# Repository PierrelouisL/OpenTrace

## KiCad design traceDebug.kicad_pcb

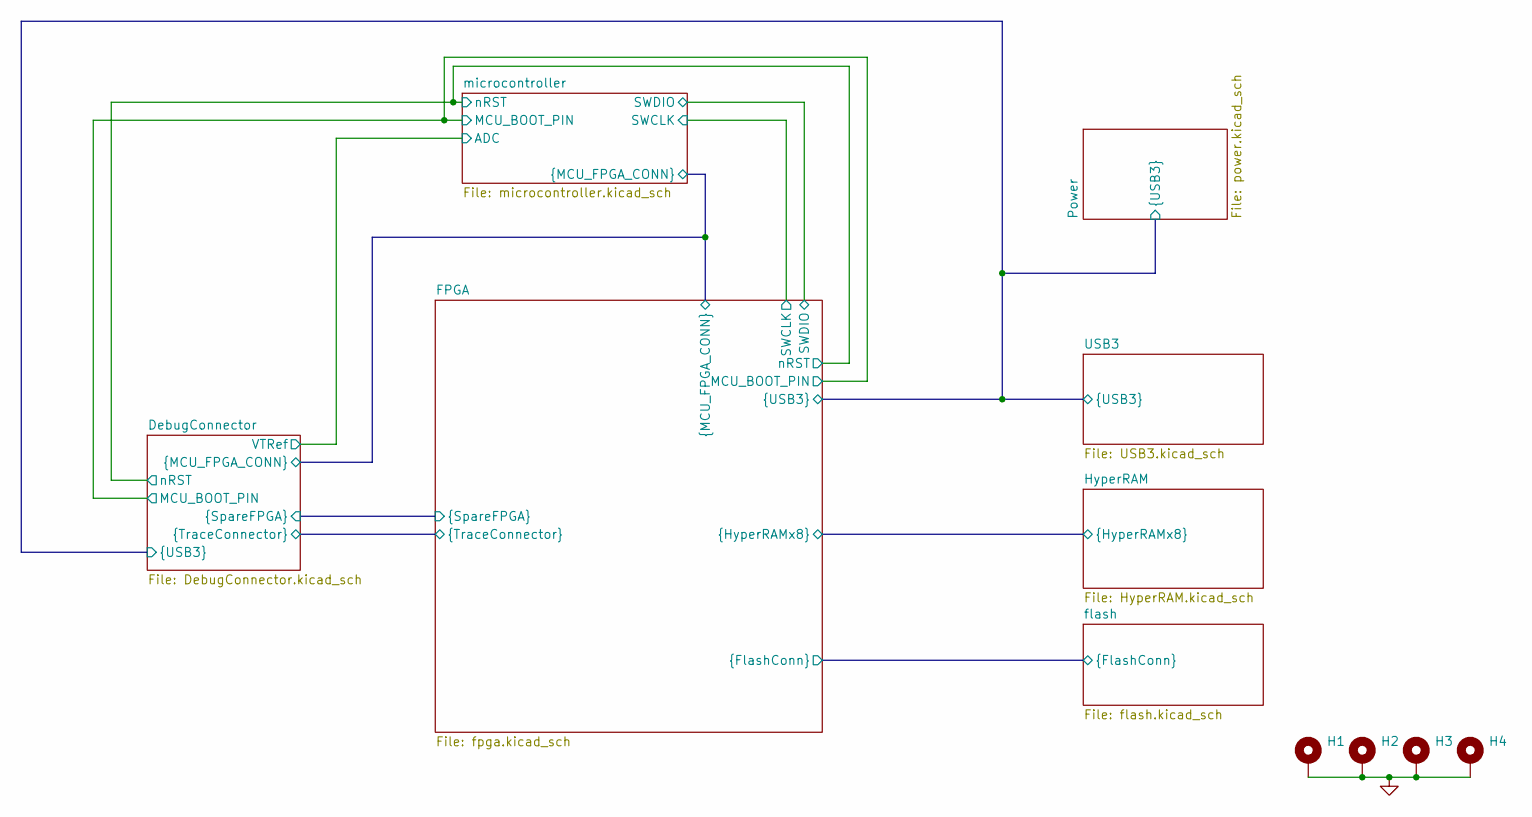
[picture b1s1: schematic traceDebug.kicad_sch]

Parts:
H1, H2, H3, H4: MountingHole_Pad; MountingHole_3.2mm_M3_Pad_Via

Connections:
GND: H1.1 (1_1), H2.1 (1_1), H3.1 (1_1), H4.1 (1_1); also elsewhere on the board

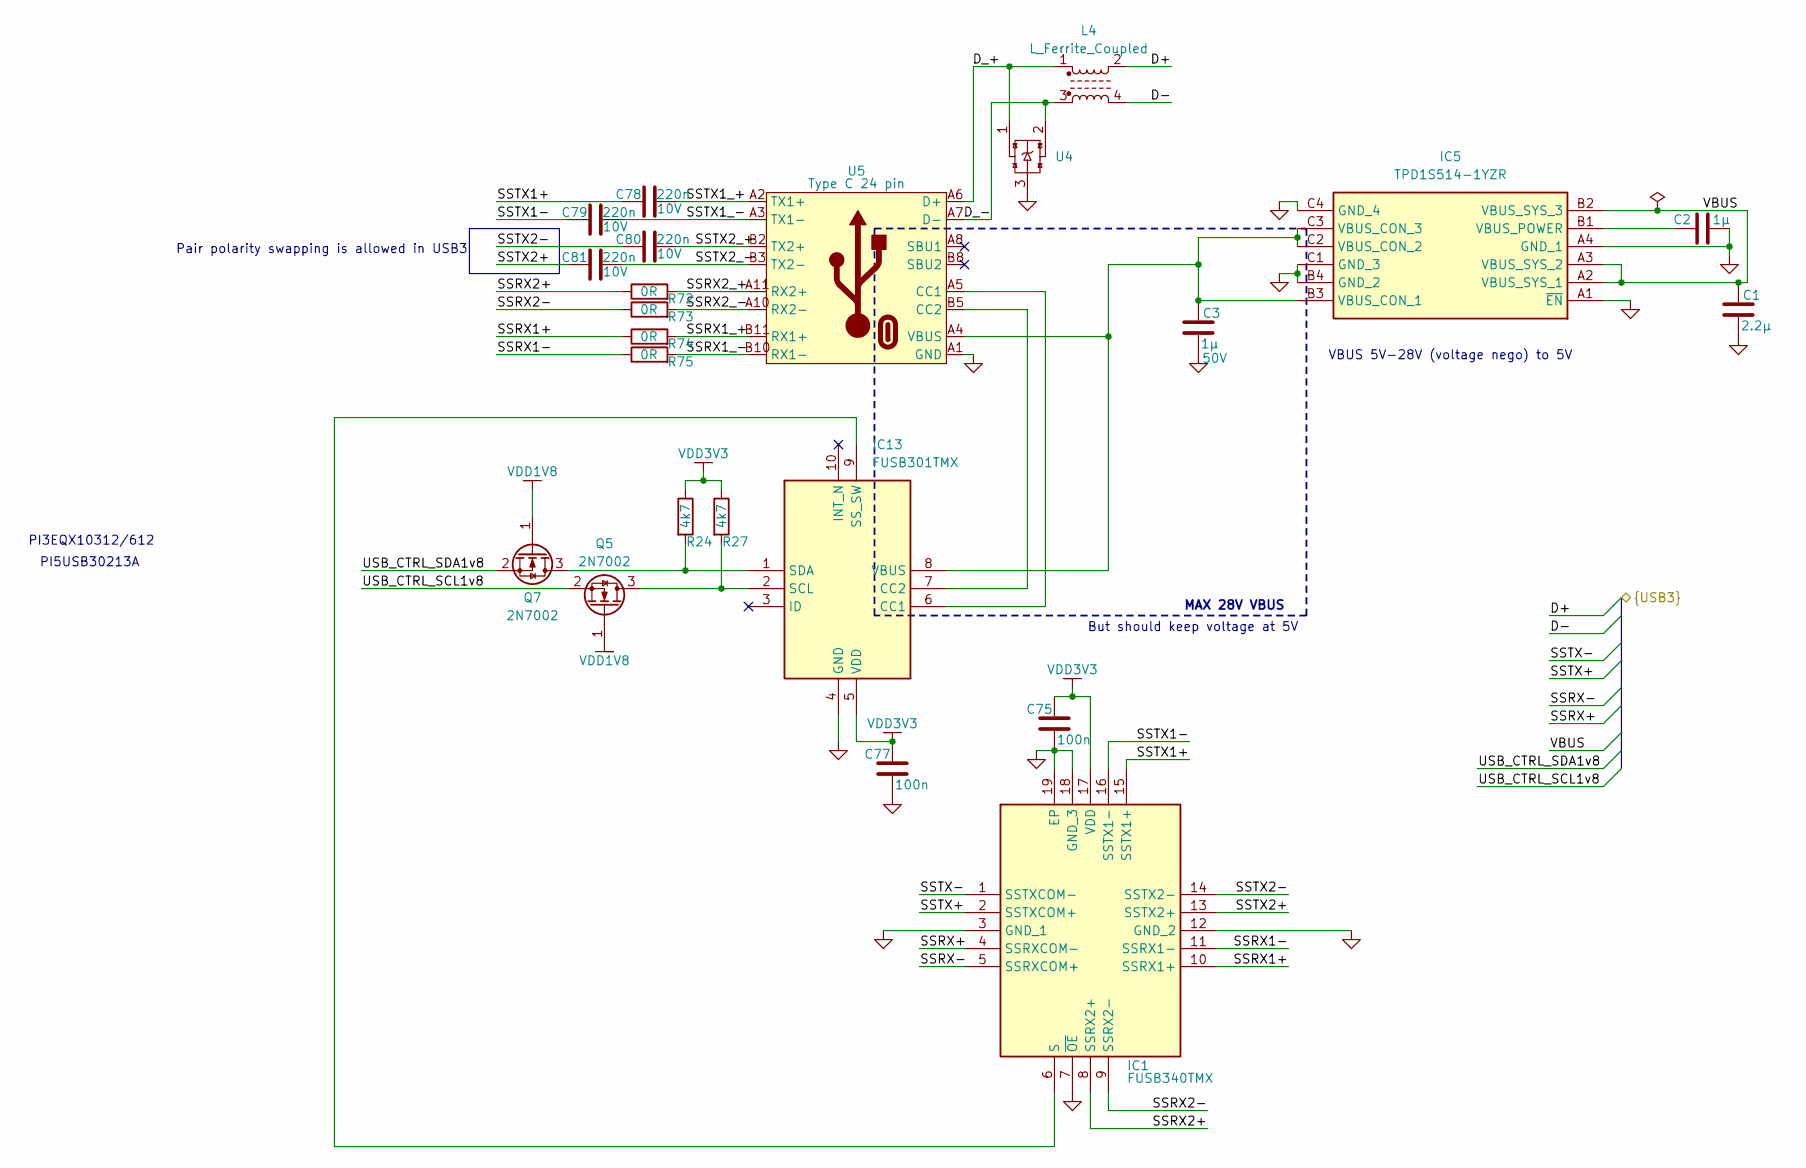
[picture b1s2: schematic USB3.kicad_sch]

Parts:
C1: 2.2µ; C_0402_1005Metric
C2: 1µ; C_0402_1005Metric
C3: 1µ; C_0402_1005Metric; Max voltage 50V
C75, C77: 100n; C_0402_1005Metric
C78, C79, C80, C81: 220n; C_0201_0603Metric; voltage 10V
IC1: FUSB340TMX; Manufacturer_Part_Number FUSB340TMX; Mouser Part Number 512-FUSB340TMX
IC5: TPD1S514-1YZR; BGA12C40P4X3_199X129X62; Manufacturer_Part_Number TPD1S514-1YZR; Mouser Part Number 595-TPD1S514-1YZR
IC13: FUSB301TMX; Manufacturer_Part_Number FUSB301TMX; Mouser Part Number 512-FUSB301TMX
L4: L_Ferrite_Coupled; C908339
Q5, Q7: 2N7002; SOT-23
R24, R27: 4k7; R_0402_1005Metric
R72, R73, R74, R75: 0R; R_0201_0603Metric
U4: C502577
U5: Type C 24 pin; USB3-2_C2762992; LCSC C2762992

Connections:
/DebugConnector/D+: L4.2; also elsewhere on the board
/DebugConnector/D-: L4.4; also elsewhere on the board
/DebugConnector/SSRX+: IC1.4 (SSRXCOM-); also elsewhere on the board
/DebugConnector/SSRX-: IC1.5 (SSRXCOM+); also elsewhere on the board
/DebugConnector/SSTX+: IC1.2 (SSTXCOM+); also elsewhere on the board
/DebugConnector/SSTX-: IC1.1 (SSTXCOM-); also elsewhere on the board
/DebugConnector/USB_CTRL_SCL1v8: Q5.2 (S); also elsewhere on the board
/DebugConnector/USB_CTRL_SDA1v8: Q7.2 (S); also elsewhere on the board
/DebugConnector/VBUS: C1.2, IC5.A2 (VBUS_SYS_1), IC5.A3 (VBUS_SYS_2), IC5.B2 (VBUS_SYS_3); also elsewhere on the board
/USB3/D_+: L4.1, U4.1, U5.A6 (D+), U5.B6 (D+)
/USB3/D_-: L4.3, U4.2, U5.A7 (D-), U5.B7 (D-)
/USB3/SSRX1+: IC1.10 (SSRX1+), R74.1
/USB3/SSRX1-: IC1.11 (SSRX1-), R75.1
/USB3/SSRX1_+: R74.2, U5.B11 (RX1+)
/USB3/SSRX1_-: R75.2, U5.B10 (RX1-)
/USB3/SSRX2+: IC1.8 (SSRX2+), R72.1
/USB3/SSRX2-: IC1.9 (SSRX2-), R73.1
/USB3/SSRX2_+: R72.2, U5.A11 (RX2+)
/USB3/SSRX2_-: R73.2, U5.A10 (RX2-)
/USB3/SSTX1+: C78.1, IC1.15 (SSTX1+)
/USB3/SSTX1-: C79.1, IC1.16 (SSTX1-)
/USB3/SSTX1_+: C78.2, U5.A2 (TX1+)
/USB3/SSTX1_-: C79.2, U5.A3 (TX1-)
/USB3/SSTX2+: C81.1, IC1.13 (SSTX2+)
/USB3/SSTX2-: C80.1, IC1.14 (SSTX2-)
/USB3/SSTX2_+: C80.2, U5.B2 (TX2+)
/USB3/SSTX2_-: C81.2, U5.B3 (TX2-)
GND: C1.1, C2.1, C3.1, C75.2, C77.2, IC1.3 (GND_1), IC1.7 (~OE), IC1.12 (GND_2), IC1.18 (GND_3), IC1.19 (EP), IC5.A1 (~EN), IC5.A4 (GND_1), IC5.B4 (GND_2), IC5.C1 (GND_3), IC5.C4 (GND_4), IC13.4 (GND), U4.3, U5.25 (GND), U5.26 (GND), U5.27 (GND), U5.28 (GND), U5.A1 (GND), U5.A12 (GND), U5.B1 (GND), U5.B12 (GND); also elsewhere on the board
unnamed: IC1.6 (S), IC13.9 (SS_SW)
unnamed: C2.2, IC5.B1 (VBUS_POWER)
unnamed: IC13.6 (CC1), U5.A5 (CC1)
unnamed: IC13.7 (CC2), U5.B5 (CC2)
unnamed: IC13.2 (SCL), Q5.3 (D), R27.2
unnamed: IC13.1 (SDA), Q7.3 (D), R24.2
unnamed: C3.2, IC5.B3 (VBUS_CON_1), IC5.C2 (VBUS_CON_2), IC5.C3 (VBUS_CON_3), IC13.8 (VBUS), U5.A4 (VBUS), U5.A9 (VBUS), U5.B4 (VBUS), U5.B9 (VBUS)
VDD1V8: Q5.1 (G), Q7.1 (G); also elsewhere on the board
VDD3V3: C75.1, C77.1, IC1.17 (VDD), IC13.5 (VDD), R24.1, R27.1; also elsewhere on the board

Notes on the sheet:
PI5USB30213A
MAX 28V VBUS
But should keep voltage at 5V
VBUS 5V-28V (voltage nego) to 5V
Pair polarity swapping is allowed in USB3
PI3EQX10312/612

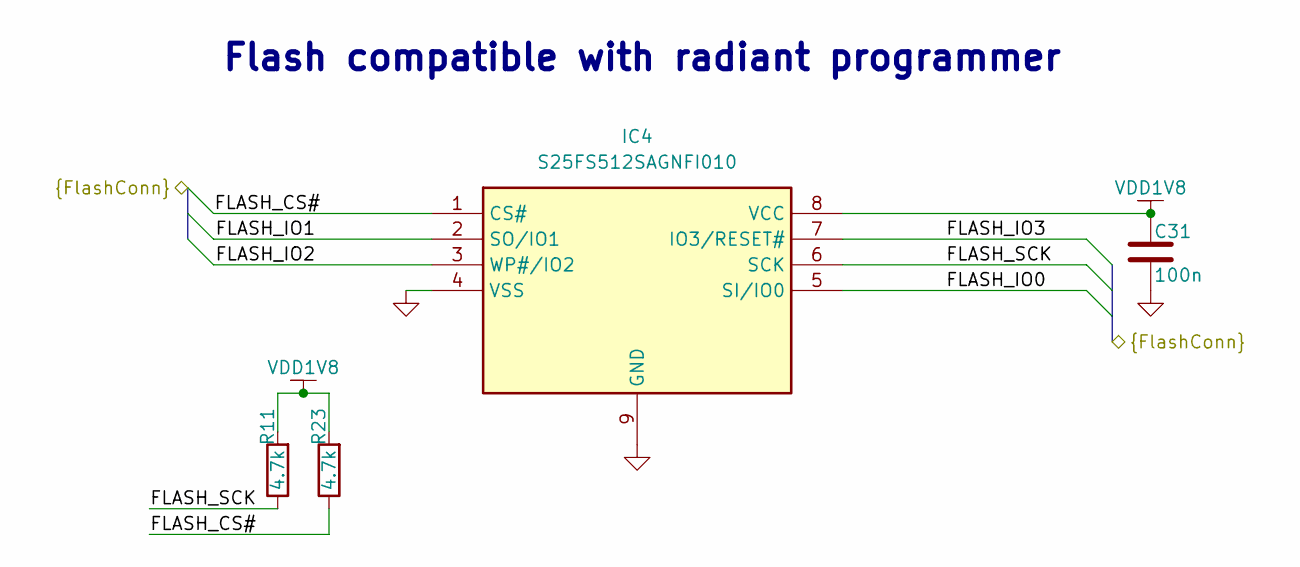
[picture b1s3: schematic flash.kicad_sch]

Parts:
C31: 100n; C_0402_1005Metric
IC4: S25FS512SAGNFI010; SON127P800X600X80-9N-D; Manufacturer_Part_Number S25FS512SAGNFI010; Mouser Part Number 727-25FS512SAGNFI010
R11, R23: 4.7k; R_0402_1005Metric

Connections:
/FPGA/FLASH_CS#: IC4.1 (CS#), R23.1; also elsewhere on the board
/FPGA/FLASH_IO0: IC4.5 (SI/IO0); also elsewhere on the board
/FPGA/FLASH_IO1: IC4.2 (SO/IO1); also elsewhere on the board
/FPGA/FLASH_IO2: IC4.3 (WP#/IO2); also elsewhere on the board
/FPGA/FLASH_IO3: IC4.7 (IO3/RESET#); also elsewhere on the board
/FPGA/FLASH_SCK: IC4.6 (SCK), R11.1; also elsewhere on the board
GND: C31.2, IC4.4 (VSS), IC4.9 (GND); also elsewhere on the board
VDD1V8: C31.1, IC4.8 (VCC), R11.2, R23.2; also elsewhere on the board

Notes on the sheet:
Flash compatible with radiant programmer

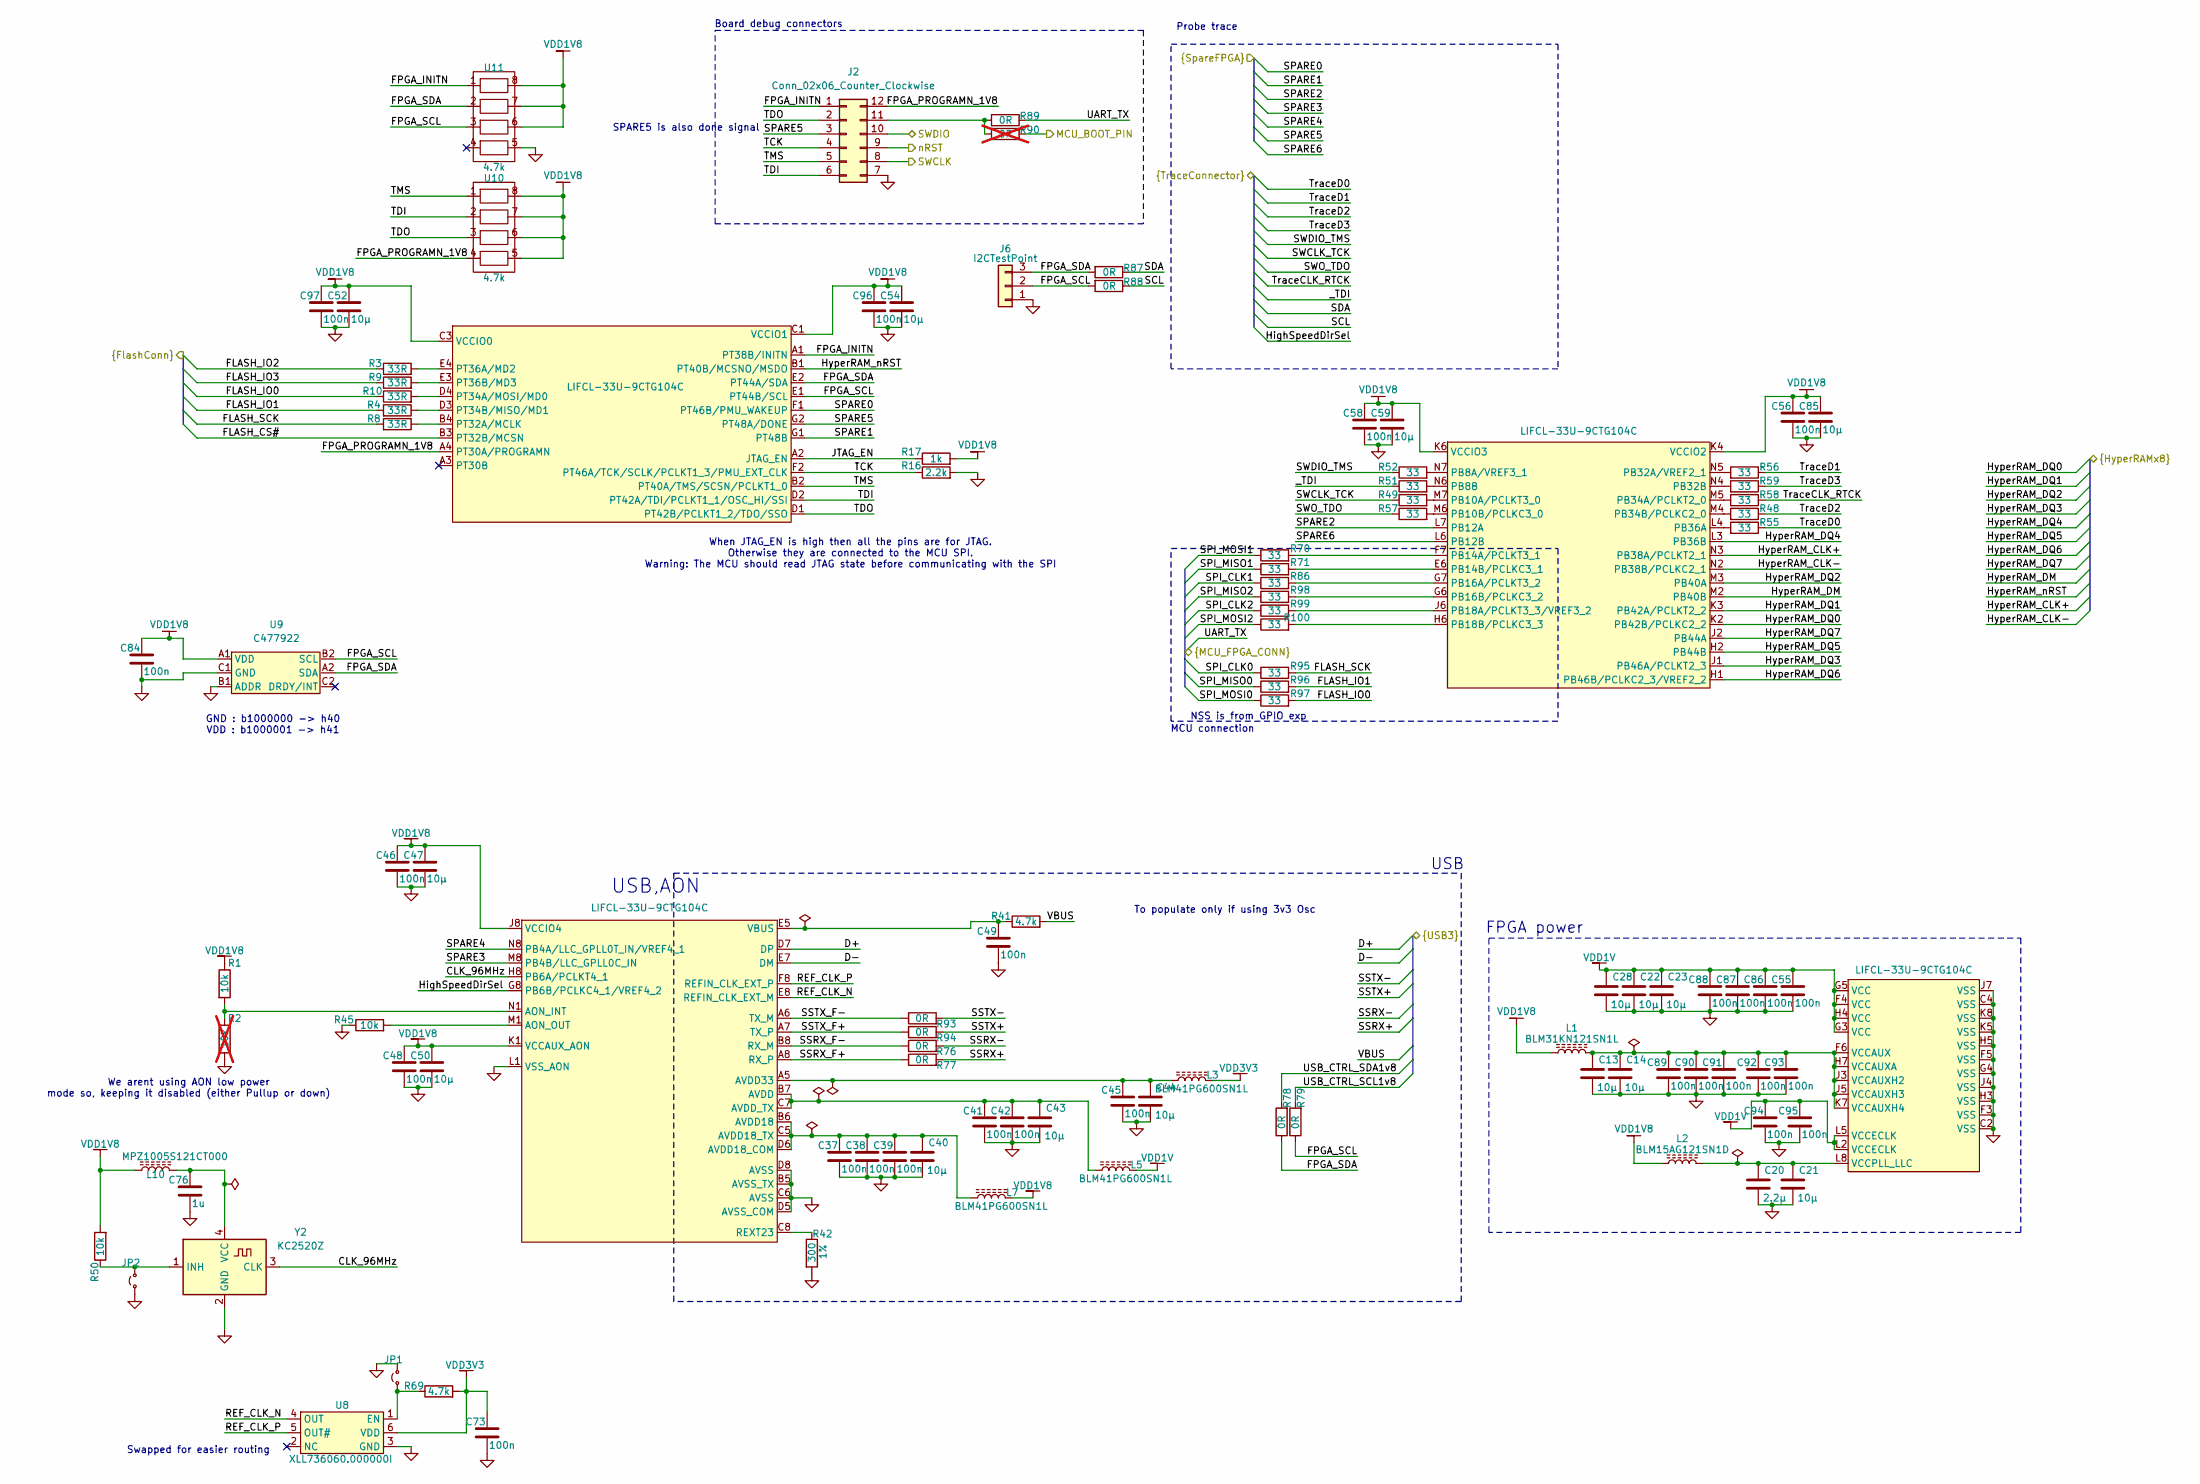
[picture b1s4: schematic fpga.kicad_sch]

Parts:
C13, C14, C21, C22, C23, C28, C40, C43, C44, C47, C50, C52, C54, C59, C85: 10µ; C_0402_1005Metric
C20: 2.2µ; C_0402_1005Metric
C37, C38, C39, C41, C42, C45, C46, C48, C49, C55, C56, C58, C86, C87, C88, C89, C90, C91, C92, C93, C94, C95, C96, C97: 100n; C_0201_0603Metric
C73, C84: 100n; C_0402_1005Metric
C76: 1u; C_0402_1005Metric
J2: Conn_02x06_Counter_Clockwise; PinHeader_2x06_P2.54mm_Vertical
J6: I2CTestPoint; PinHeader_1x03_P2.54mm_Vertical
JP1, JP2: Jumper_2_Small_Open; PinHeader_1x02_P2.54mm_Vertical
L1: BLM31KN121SN1L; L_1206_3216Metric
L2: BLM15AG121SN1D; L_0402_1005Metric
L3, L5, L7: BLM41PG600SN1L; L_1806_4516Metric
L10: MPZ1005S121CT000; L_0402_1005Metric
R1, R45, R50: 10k; R_0402_1005Metric
R2: 10k; R_0402_1005Metric; not fitted
R3, R4, R8, R9, R10: 33R; R_0402_1005Metric
R16: 2.2k; R_0402_1005Metric
R17: 1k; R_0402_1005Metric
R41, R69: 4.7k; R_0402_1005Metric
R42: 300; R_0402_1005Metric
R48, R49, R51, R52, R55, R56, R57, R58, R59, R70, R71, R86, R95, R96, R97, R98, R99, R100: 33; R_0402_1005Metric
R76, R77, R93, R94: 0R; R_0201_0603Metric
R78, R79, R87, R88, R89: 0R; R_0402_1005Metric
R90: 0R; R_0402_1005Metric; not fitted
U1: LIFCL-33U-9CTG104C; BGA104C65P8X13_550X850X97
U8: XLL736060.000000I; Renesas_XLL
U9: C477922; DSBGA-6; LCSC C477922
U10, U11: 4.7k; C876943; LCSC C876943
Y2: KC2520Z; Oscillator_SMD_Kyocera_KC2520Z-4Pin_2.5x2.0mm; mouser ref KC2520Z96.0000C1KX00

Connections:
/DebugConnector/D+: U1.D7 (DP); also elsewhere on the board
/DebugConnector/D-: U1.E7 (DM); also elsewhere on the board
/DebugConnector/HighSpeedDirSel: U1.G8 (PB6B/PCLKC4_1/VREF4_2); also elsewhere on the board
/DebugConnector/MCU_BOOT_PIN: R90.1; also elsewhere on the board
/DebugConnector/SCL: R88.1; also elsewhere on the board
/DebugConnector/SDA: R87.1; also elsewhere on the board
/DebugConnector/SPARE0: U1.F1 (PT46B/PMU_WAKEUP); also elsewhere on the board
/DebugConnector/SPARE1: U1.G1 (PT48B); also elsewhere on the board
/DebugConnector/SPARE2: U1.L7 (PB12A); also elsewhere on the board
/DebugConnector/SPARE3: U1.M8 (PB4B/LLC_GPLL0C_IN); also elsewhere on the board
/DebugConnector/SPARE4: U1.N8 (PB4A/LLC_GPLL0T_IN/VREF4_1); also elsewhere on the board
/DebugConnector/SPARE5: J2.3, U1.G2 (PT48A/DONE); also elsewhere on the board
/DebugConnector/SPARE6: U1.L6 (PB12B); also elsewhere on the board
/DebugConnector/SPI_CLK0: R95.1; also elsewhere on the board
/DebugConnector/SPI_CLK1: R86.1; also elsewhere on the board
/DebugConnector/SPI_CLK2: R99.1; also elsewhere on the board
/DebugConnector/SPI_MISO0: R96.1; also elsewhere on the board
/DebugConnector/SPI_MISO1: R71.1; also elsewhere on the board
/DebugConnector/SPI_MISO2: R98.1; also elsewhere on the board
/DebugConnector/SPI_MOSI0: R97.1; also elsewhere on the board
/DebugConnector/SPI_MOSI1: R70.1; also elsewhere on the board
/DebugConnector/SPI_MOSI2: R100.1; also elsewhere on the board
/DebugConnector/SSRX+: R77.2; also elsewhere on the board
/DebugConnector/SSRX-: R76.2; also elsewhere on the board
/DebugConnector/SSTX+: R94.2; also elsewhere on the board
/DebugConnector/SSTX-: R93.2; also elsewhere on the board
/DebugConnector/SWCLK_TCK: R49.1; also elsewhere on the board
/DebugConnector/SWDIO_TMS: R52.1; also elsewhere on the board
/DebugConnector/SWO_TDO: R57.1; also elsewhere on the board
/DebugConnector/TraceCLK_RTCK: R58.1; also elsewhere on the board
/DebugConnector/TraceD0: R55.1; also elsewhere on the board
/DebugConnector/TraceD1: R56.1; also elsewhere on the board
/DebugConnector/TraceD2: R48.1; also elsewhere on the board
/DebugConnector/TraceD3: R59.1; also elsewhere on the board
/DebugConnector/UART_TX: R89.1; also elsewhere on the board
/DebugConnector/USB_CTRL_SCL1v8: R79.2; also elsewhere on the board
/DebugConnector/USB_CTRL_SDA1v8: R78.2; also elsewhere on the board
/DebugConnector/VBUS: R41.2; also elsewhere on the board
/DebugConnector/_TDI: R51.1; also elsewhere on the board
/DebugConnector/nRST: J2.9; also elsewhere on the board
/FPGA/CLK_96MHz: U1.H8 (PB6A/PCLKT4_1), Y2.3 (CLK)
/FPGA/FLASH_CS#: U1.B3 (PT32B/MCSN); also elsewhere on the board
/FPGA/FLASH_IO0: R10.1, R97.2; also elsewhere on the board
/FPGA/FLASH_IO1: R4.2, R96.2; also elsewhere on the board
/FPGA/FLASH_IO2: R3.1; also elsewhere on the board
/FPGA/FLASH_IO3: R9.1; also elsewhere on the board
/FPGA/FLASH_SCK: R8.2, R95.2; also elsewhere on the board
/FPGA/FPGA_INITN: J2.1, U1.A1 (PT38B/INITN), U11.1
/FPGA/FPGA_PROGRAMN_1V8: J2.12, U1.A4 (PT30A/PROGRAMN), U10.4
/FPGA/FPGA_SCL: J6.2, R79.1, R88.2, U1.E1 (PT44B/SCL), U9.B2 (SCL), U11.3
/FPGA/FPGA_SDA: J6.3, R78.1, R87.2, U1.E2 (PT44A/SDA), U9.A2 (SDA), U11.2
/FPGA/HyperRAM_CLK+: U1.N3 (PB38A/PCLKT2_1); also elsewhere on the board
/FPGA/HyperRAM_CLK-: U1.N2 (PB38B/PCLKC2_1); also elsewhere on the board
/FPGA/HyperRAM_DM: U1.M2 (PB40B); also elsewhere on the board
/FPGA/HyperRAM_DQ0: U1.K2 (PB42B/PCLKC2_2); also elsewhere on the board
/FPGA/HyperRAM_DQ1: U1.K3 (PB42A/PCLKT2_2); also elsewhere on the board
/FPGA/HyperRAM_DQ2: U1.M3 (PB40A); also elsewhere on the board
/FPGA/HyperRAM_DQ3: U1.J1 (PB46A/PCLKT2_3); also elsewhere on the board
/FPGA/HyperRAM_DQ4: U1.L3 (PB36B); also elsewhere on the board
/FPGA/HyperRAM_DQ5: U1.H2 (PB44B); also elsewhere on the board
/FPGA/HyperRAM_DQ6: U1.H1 (PB46B/PCLKC2_3/VREF2_2); also elsewhere on the board
/FPGA/HyperRAM_DQ7: U1.J2 (PB44A); also elsewhere on the board
/FPGA/HyperRAM_nRST: U1.B1 (PT40B/MCSNO/MSDO); also elsewhere on the board
/FPGA/JTAG_EN: R17.1, U1.A2 (JTAG_EN)
/FPGA/REF_CLK_N: U1.E8 (REFIN_CLK_EXT_M), U8.4 (OUT)
/FPGA/REF_CLK_P: U1.F8 (REFIN_CLK_EXT_P), U8.5 (OUT#)
/FPGA/SSRX_F+: R77.1, U1.A8 (RX_P)
/FPGA/SSRX_F-: R76.1, U1.B8 (RX_M)
/FPGA/SSTX_F+: R94.1, U1.A7 (TX_P)
/FPGA/SSTX_F-: R93.1, U1.A6 (TX_M)
/FPGA/TCK: J2.4, R16.1, U1.F2 (PT46A/TCK/SCLK/PCLKT1_3/PMU_EXT_CLK)
/FPGA/TDI: J2.6, U1.D2 (PT42A/TDI/PCLKT1_1/OSC_HI/SSI), U10.2
/FPGA/TDO: J2.2, U1.D1 (PT42B/PCLKT1_2/TDO/SSO), U10.3
/FPGA/TMS: J2.5, U1.B2 (PT40A/TMS/SCSN/PCLKT1_0), U10.1
/microcontroller/SWCLK: J2.8; also elsewhere on the board
/microcontroller/SWDIO: J2.10; also elsewhere on the board
GND: C13.2, C14.2, C20.2, C21.2, C22.2, C23.2, C28.2, C37.2, C38.2, C39.2, C40.2, C41.2, C42.2, C43.2, C44.2, C45.2, C46.2, C47.2, C48.2, C49.2, C50.2, C52.2, C54.2, C55.2, C56.2, C58.2, C59.2, C73.2, C76.2, C84.2, C85.2, C86.2, C87.2, C88.2, C89.2, C90.2, C91.2, C92.2, C93.2, C94.2, C95.2, C96.2, C97.2, J2.7, J6.1, JP1.2 (B), JP2.1 (A), R2.2, R16.2, R42.2, R45.1, U1.B5 (AVSS_TX), U1.C2 (VSS), U1.C4 (VSS), U1.C6 (AVSS), U1.D5 (AVSS_COM), U1.D8 (AVSS), U1.F3 (VSS), U1.F5 (VSS), U1.G4 (VSS), U1.H3 (VSS), U1.H5 (VSS), U1.J4 (VSS), U1.J7 (VSS), U1.K5 (VSS), U1.K8 (VSS), U1.L1 (VSS_AON), U8.3 (GND), U9.B1 (ADDR), U9.C1 (GND), U11.5, Y2.2 (GND); also elsewhere on the board
unnamed: J2.11, R89.2, R90.2
unnamed: JP1.1 (A), R69.1, U8.1 (EN)
unnamed: JP2.2 (B), R50.1, Y2.1 (INH)
unnamed: R8.1, U1.B4 (PT32A/MCLK)
unnamed: R10.2, U1.D4 (PT34A/MOSI/MD0)
unnamed: R4.1, U1.D3 (PT34B/MISO/MD1)
unnamed: R3.2, U1.E4 (PT36A/MD2)
unnamed: R9.2, U1.E3 (PT36B/MD3)
unnamed: C13.1, C14.1, C89.1, C90.1, C91.1, C92.1, C93.1, L1.2, U1.F6 (VCCAUX), U1.H7 (VCCAUXA), U1.J3 (VCCAUXH2), U1.J5 (VCCAUXH3), U1.K7 (VCCAUXH4)
unnamed: C20.1, C21.1, L2.2, U1.L8 (VCCPLL_LLC)
unnamed: R1.2, R2.1, U1.N1 (AON_INT)
unnamed: R45.2, U1.M1 (AON_OUT)
unnamed: C37.1, C38.1, C39.1, C40.1, L7.1, U1.B6 (AVDD18), U1.C5 (AVDD18_TX), U1.D6 (AVDD18_COM)
unnamed: C44.1, C45.1, L3.1, U1.A5 (AVDD33)
unnamed: C41.1, C42.1, C43.1, L5.1, U1.B7 (AVDD), U1.C7 (AVDD_TX)
unnamed: R42.1, U1.C8 (REXT23)
unnamed: C49.1, R41.1, U1.E5 (VBUS)
unnamed: R52.2, U1.N7 (PB8A/VREF3_1)
unnamed: R51.2, U1.N6 (PB8B)
unnamed: R49.2, U1.M7 (PB10A/PCLKT3_0)
unnamed: R57.2, U1.M6 (PB10B/PCLKC3_0)
unnamed: R70.2, U1.F7 (PB14A/PCLKT3_1)
unnamed: R71.2, U1.E6 (PB14B/PCLKC3_1)
unnamed: R86.2, U1.G7 (PB16A/PCLKT3_2)
unnamed: R98.2, U1.G6 (PB16B/PCLKC3_2)
unnamed: R99.2, U1.J6 (PB18A/PCLKT3_3/VREF3_2)
unnamed: R100.2, U1.H6 (PB18B/PCLKC3_3)
unnamed: R56.2, U1.N5 (PB32A/VREF2_1)
unnamed: R59.2, U1.N4 (PB32B)
unnamed: R58.2, U1.M5 (PB34A/PCLKT2_0)
unnamed: R48.2, U1.M4 (PB34B/PCLKC2_0)
unnamed: R55.2, U1.L4 (PB36A)
unnamed: C76.1, L10.2, Y2.4 (VCC)
VDD1V: C22.1, C23.1, C28.1, C55.1, C86.1, C87.1, C88.1, C94.1, C95.1, L5.2, U1.F4 (VCC), U1.G3 (VCC), U1.G5 (VCC), U1.H4 (VCC), U1.L2 (VCCECLK), U1.L5 (VCCECLK); also elsewhere on the board
VDD1V8: C46.1, C47.1, C48.1, C50.1, C52.1, C54.1, C56.1, C58.1, C59.1, C84.1, C85.1, C96.1, C97.1, L1.1, L2.1, L7.2, L10.1, R1.1, R17.2, R50.2, U1.C1 (VCCIO1), U1.C3 (VCCIO0), U1.J8 (VCCIO4), U1.K1 (VCCAUX_AON), U1.K4 (VCCIO2), U1.K6 (VCCIO3), U9.A1 (VDD), U10.5, U10.6, U10.7, U10.8, U11.6, U11.7, U11.8; also elsewhere on the board
VDD3V3: C73.1, L3.2, R69.2, U8.6 (VDD); also elsewhere on the board

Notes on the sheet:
NSS is from GPIO exp
Board debug connectors
USB
USB,AON
Swapped for easier routing
MCU connection
Probe trace
SPARE5 is also done signal
When JTAG_EN is high then all the pins are for JTAG. Otherwise they are connected to the MCU SPI. Warning: The MCU should read JTAG state before communicating with the SPI
To populate only if using 3v3 Osc
We arent using AON low power mode so, keeping it disabled (either Pullup or down)
GND : b1000000 -> h40 VDD : b1000001 -> h41
FPGA power

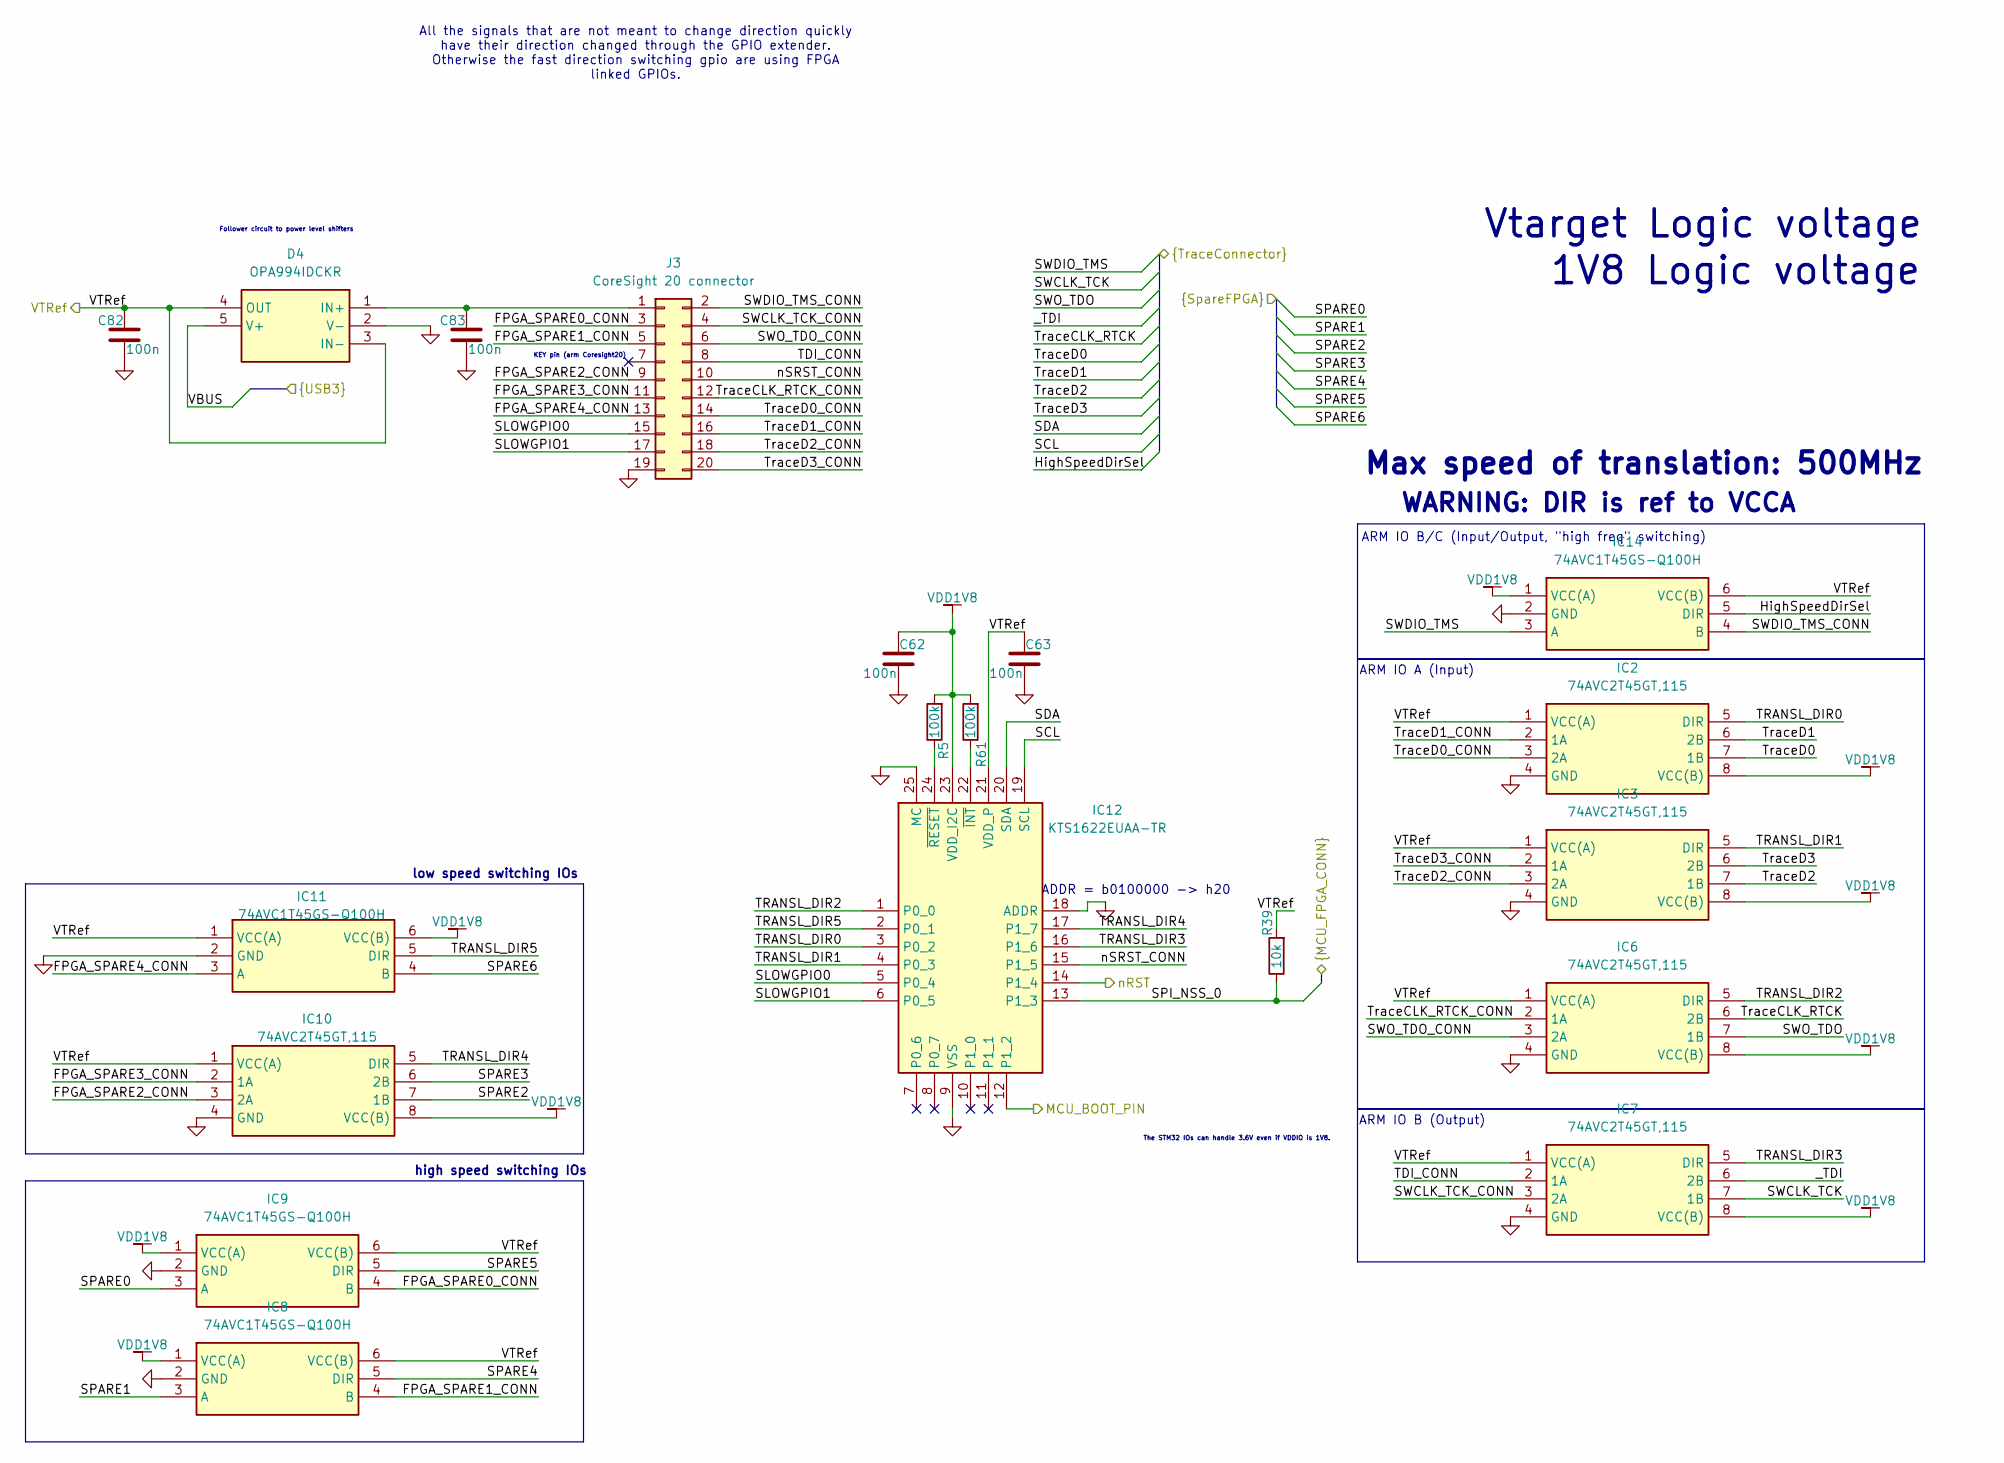
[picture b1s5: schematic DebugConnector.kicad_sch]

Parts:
C62, C63, C82, C83: 100n; C_0402_1005Metric
D4: OPA994IDCKR; SOT65P210X110-5N; Manufacturer_Part_Number OPA994IDCKR
IC2, IC3, IC6, IC7, IC10: 74AVC2T45GT,115; 74AVC9112GTX; Manufacturer_Part_Number 74AVC2T45GT,115; Mouser Part Number 771-AVC2T45GT115
IC8, IC9, IC11, IC14: 74AVC1T45GS-Q100H; 74LVC1G3157GS132; Manufacturer_Part_Number 74AVC1T45GS-Q100H; Mouser Part Number 771-AVC1T45GSQ100H
IC12: KTS1622EUAA-TR; QFN50P400X400X80-25N-D; Manufacturer_Part_Number KTS1622EUAA-TR; Mouser Part Number 389-KTS1622EUAA-TR
J3: CoreSight 20 connector; PinHeader_2x10_P2.54mm_Horizontal
R5, R61: 100k; R_0402_1005Metric
R39: 10k; R_0402_1005Metric

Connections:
/DebugConnector/FPGA_SPARE0_CONN: IC9.4 (B), J3.3
/DebugConnector/FPGA_SPARE1_CONN: IC8.4 (B), J3.5
/DebugConnector/FPGA_SPARE2_CONN: IC10.3 (2A), J3.9
/DebugConnector/FPGA_SPARE3_CONN: IC10.2 (1A), J3.11
/DebugConnector/FPGA_SPARE4_CONN: IC11.3 (A), J3.13
/DebugConnector/HighSpeedDirSel: IC14.5 (DIR); also elsewhere on the board
/DebugConnector/MCU_BOOT_PIN: IC12.12 (P1_2); also elsewhere on the board
/DebugConnector/SCL: IC12.19 (SCL); also elsewhere on the board
/DebugConnector/SDA: IC12.20 (SDA); also elsewhere on the board
/DebugConnector/SLOWGPIO0: IC12.5 (P0_4), J3.15
/DebugConnector/SLOWGPIO1: IC12.6 (P0_5), J3.17
/DebugConnector/SPARE0: IC9.3 (A); also elsewhere on the board
/DebugConnector/SPARE1: IC8.3 (A); also elsewhere on the board
/DebugConnector/SPARE2: IC10.7 (1B); also elsewhere on the board
/DebugConnector/SPARE3: IC10.6 (2B); also elsewhere on the board
/DebugConnector/SPARE4: IC8.5 (DIR); also elsewhere on the board
/DebugConnector/SPARE5: IC9.5 (DIR); also elsewhere on the board
/DebugConnector/SPARE6: IC11.4 (B); also elsewhere on the board
/DebugConnector/SPI_NSS_0: IC12.13 (P1_3), R39.1; also elsewhere on the board
/DebugConnector/SWCLK_TCK: IC7.7 (1B); also elsewhere on the board
/DebugConnector/SWCLK_TCK_CONN: IC7.3 (2A), J3.4
/DebugConnector/SWDIO_TMS: IC14.3 (A); also elsewhere on the board
/DebugConnector/SWDIO_TMS_CONN: IC14.4 (B), J3.2
/DebugConnector/SWO_TDO: IC6.7 (1B); also elsewhere on the board
/DebugConnector/SWO_TDO_CONN: IC6.3 (2A), J3.6
/DebugConnector/TDI_CONN: IC7.2 (1A), J3.8
/DebugConnector/TRANSL_DIR0: IC2.5 (DIR), IC12.3 (P0_2)
/DebugConnector/TRANSL_DIR1: IC3.5 (DIR), IC12.4 (P0_3)
/DebugConnector/TRANSL_DIR2: IC6.5 (DIR), IC12.1 (P0_0)
/DebugConnector/TRANSL_DIR3: IC7.5 (DIR), IC12.16 (P1_6)
/DebugConnector/TRANSL_DIR4: IC10.5 (DIR), IC12.17 (P1_7)
/DebugConnector/TRANSL_DIR5: IC11.5 (DIR), IC12.2 (P0_1)
/DebugConnector/TraceCLK_RTCK: IC6.6 (2B); also elsewhere on the board
/DebugConnector/TraceCLK_RTCK_CONN: IC6.2 (1A), J3.12
/DebugConnector/TraceD0: IC2.7 (1B); also elsewhere on the board
/DebugConnector/TraceD0_CONN: IC2.3 (2A), J3.14
/DebugConnector/TraceD1: IC2.6 (2B); also elsewhere on the board
/DebugConnector/TraceD1_CONN: IC2.2 (1A), J3.16
/DebugConnector/TraceD2: IC3.7 (1B); also elsewhere on the board
/DebugConnector/TraceD2_CONN: IC3.3 (2A), J3.18
/DebugConnector/TraceD3: IC3.6 (2B); also elsewhere on the board
/DebugConnector/TraceD3_CONN: IC3.2 (1A), J3.20
/DebugConnector/VBUS: D4.5 (V+); also elsewhere on the board
/DebugConnector/VTRef: C63.1, C82.1, D4.3 (IN-), D4.4 (OUT), IC2.1 (VCC(A)), IC3.1 (VCC(A)), IC6.1 (VCC(A)), IC7.1 (VCC(A)), IC8.6 (VCC(B)), IC9.6 (VCC(B)), IC10.1 (VCC(A)), IC11.1 (VCC(A)), IC12.21 (VDD_P), IC14.6 (VCC(B)), R39.2; also elsewhere on the board
/DebugConnector/_TDI: IC7.6 (2B); also elsewhere on the board
/DebugConnector/nRST: IC12.14 (P1_4); also elsewhere on the board
/DebugConnector/nSRST_CONN: IC12.15 (P1_5), J3.10
GND: C62.2, C63.2, C82.2, C83.2, D4.2 (V-), IC2.4 (GND), IC3.4 (GND), IC6.4 (GND), IC7.4 (GND), IC8.2 (GND), IC9.2 (GND), IC10.4 (GND), IC11.2 (GND), IC12.9 (VSS), IC12.18 (ADDR), IC12.25 (MC), IC14.2 (GND), J3.19; also elsewhere on the board
unnamed: C83.1, D4.1 (IN+), J3.1
unnamed: IC12.22 (~INT), R61.1
unnamed: IC12.24 (~RESET), R5.1
VDD1V8: C62.1, IC2.8 (VCC(B)), IC3.8 (VCC(B)), IC6.8 (VCC(B)), IC7.8 (VCC(B)), IC8.1 (VCC(A)), IC9.1 (VCC(A)), IC10.8 (VCC(B)), IC11.6 (VCC(B)), IC12.23 (VDD_I2C), IC14.1 (VCC(A)), R5.2, R61.2; also elsewhere on the board

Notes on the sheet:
Follower circuit to power level shifters
Max speed of translation: 500MHz
low speed switching IOs
1V8 Logic voltage
All the signals that are not meant to change direction quickly have their direction changed through the GPIO extender. Otherwise the fast direction switching gpio are using FPGA linked GPIOs.
KEY pin (arm Coresight20)
ADDR = b0100000 -> h20
WARNING: DIR is ref to VCCA
ARM IO B/C (Input/Output, "high freq" switching)
high speed switching IOs
Vtarget Logic voltage
ARM IO B (Output)
ARM IO A (Input)
The STM32 IOs can handle 3.6V even if VDDIO is 1V8.

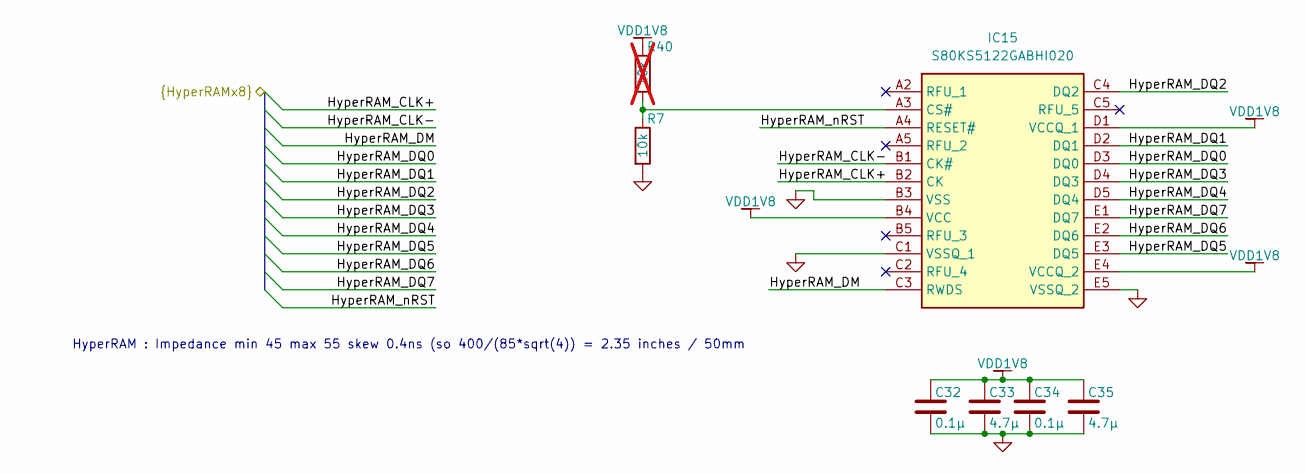
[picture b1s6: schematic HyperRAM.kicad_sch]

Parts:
C32, C34: 0.1µ; C_0402_1005Metric
C33, C35: 4.7µ; C_0402_1005Metric
IC15: S80KS5122GABHI020; BGA24C100P5X5_600X800X100; Manufacturer_Part_Number S80KS5122GABHI020; Mouser Part Number 727-S5122GABHI020
R7: 10k; R_0402_1005Metric
R40: 10k; R_0402_1005Metric; not fitted

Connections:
/FPGA/HyperRAM_CLK+: IC15.B2 (CK); also elsewhere on the board
/FPGA/HyperRAM_CLK-: IC15.B1 (CK#); also elsewhere on the board
/FPGA/HyperRAM_DM: IC15.C3 (RWDS); also elsewhere on the board
/FPGA/HyperRAM_DQ0: IC15.D3 (DQ0); also elsewhere on the board
/FPGA/HyperRAM_DQ1: IC15.D2 (DQ1); also elsewhere on the board
/FPGA/HyperRAM_DQ2: IC15.C4 (DQ2); also elsewhere on the board
/FPGA/HyperRAM_DQ3: IC15.D4 (DQ3); also elsewhere on the board
/FPGA/HyperRAM_DQ4: IC15.D5 (DQ4); also elsewhere on the board
/FPGA/HyperRAM_DQ5: IC15.E3 (DQ5); also elsewhere on the board
/FPGA/HyperRAM_DQ6: IC15.E2 (DQ6); also elsewhere on the board
/FPGA/HyperRAM_DQ7: IC15.E1 (DQ7); also elsewhere on the board
/FPGA/HyperRAM_nRST: IC15.A4 (RESET#); also elsewhere on the board
GND: C32.2, C33.2, C34.2, C35.2, IC15.B3 (VSS), IC15.C1 (VSSQ_1), IC15.E5 (VSSQ_2), R7.2; also elsewhere on the board
unnamed: IC15.A3 (CS#), R7.1, R40.2
VDD1V8: C32.1, C33.1, C34.1, C35.1, IC15.B4 (VCC), IC15.D1 (VCCQ_1), IC15.E4 (VCCQ_2), R40.1; also elsewhere on the board

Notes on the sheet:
HyperRAM : Impedance min 45 max 55 skew 0.4ns (so 400/(85*sqrt(4)) = 2.35 inches / 50mm
